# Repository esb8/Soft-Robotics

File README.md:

# Soft Robotics PCB

Motor control, optical feedback, ADCs, sensors, servos, and a camera on a single board.  
This project features a soft-robotics controller built around an ESP32 with an onboard camera, driver stages for multiple electromagnets, photoresistor sensing, SPI breakouts, and a UART header for easy flashing.

## Features
- **ESP32** (WROOM or WROVER) with **camera module** (OV2640 or similar)
- **4–8 electromagnet channels** with protected low-side MOSFET drivers (PWM capable)
- **Photoresistor (LDR) inputs** with RC dividers → ADC
- **SPI header** (3.3V) for add-ons (external ADCs, sensors, or LED drivers)
- **Dedicated UART header** for flashing (RTS/DTR optional) + **USB-C** or JST-PH power
- **Reverse-polarity & transient protection**, per-channel flyback/snubbers
- **Buck Regulation for 2S LiPos**
- **Mounting + cable-reliefs** sized for soft-robotics rigs
- **Full Codebase** containing all peripheral test code

## Media
### Schematic 

### PCB Layout

### Front View

### Back View

### Setup Guidelines
1. Open ArduinoIDE
2. Set Baud Rate: 115200
3. Set COM to whatever appears on device manager
4. Set board to ESP32S3-Dev Board.
5. The serial monitor must read at 115200 Baud.
### Boot Guide
1. Enter Bootloader
2. Ensure IO46 is pulled down.
3. Pull boot low (Switch ON), Pull Enable Up and Down to reset the ESP32 (Switch On -> Switch Off). During this time firmware can be uploaded.
4. Boot from uploaded code
4. Pull boot high (Switch OFF), Pull Enable Up and Down to reset the ESP32 (Switch On -> Switch Off).

## Pinout
- CAMERA: PINS 4 to 14, 21.
- CAM_SDA: IO20
- CAM_SCL: IO3
- S_PWM: IO1, ADC1_CH0
- SDA: IO42
- SCL: IO41
- XSHUT: IO40
- nFault_A: I039
- nFault_B: IO4
- I_SENSE_A: IO14, ADC_CH3
- I_SENSE_B: IO2, ADC1_CH0
- IN1_A: IO38
- IN2_A: IO48
- IN1_B: IO47
- IN2_B: IO21
- LDR1: IO19
- LDR2: IO5
  
## Calculations

### Trip Current (typ.)
I_TRIP = V_REF / (R_IPROPI × A_IPROPI)  
       = 3.3 / (2350 × 455 × 10^-6)  
       ≈ 3.09 A

### IPROPI Current at Trip
I_IPROPI = I_TRIP × A_IPROPI  
         = V_REF / R_IPROPI  
         = 3.3 / 2350  
         ≈ 1.40 mA

### IPROPI Voltage at Trip
V_IPROPI = I_IPROPI × R_IPROPI  
         = 3.3 V

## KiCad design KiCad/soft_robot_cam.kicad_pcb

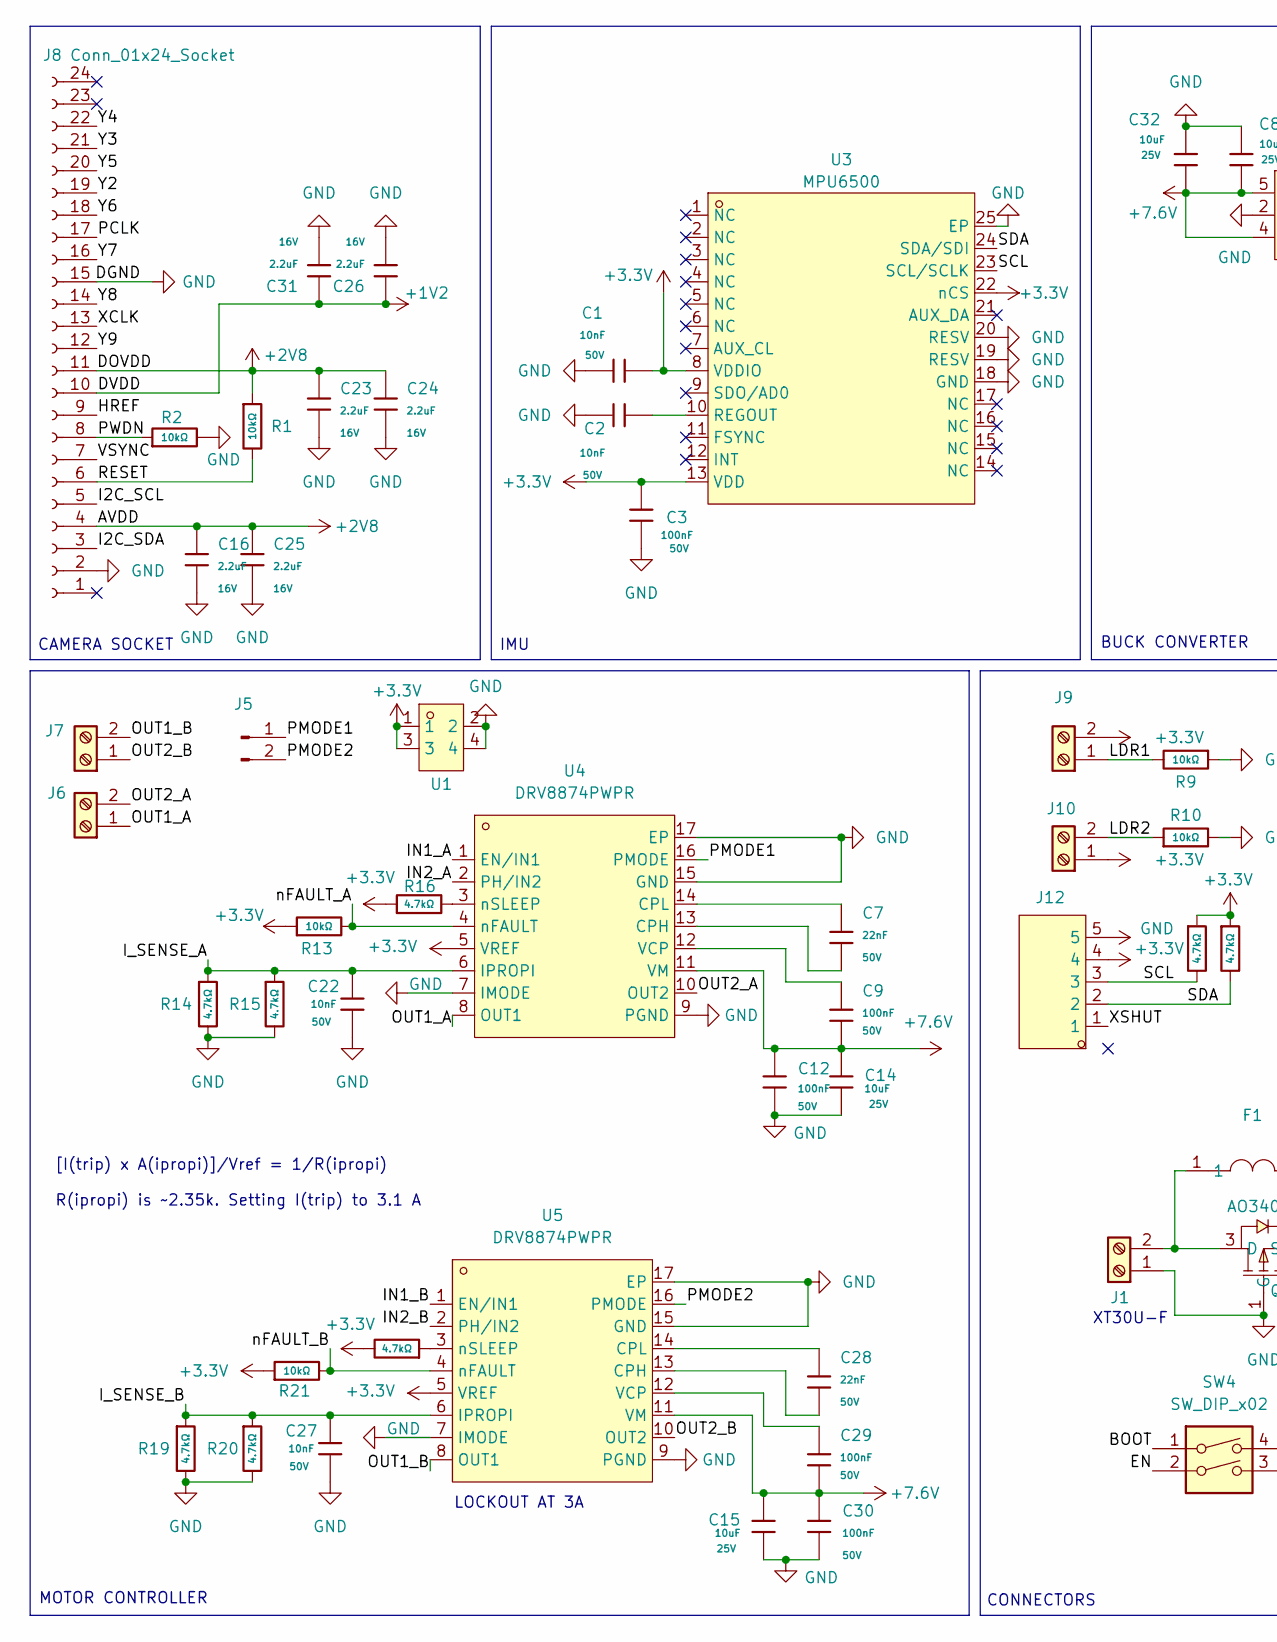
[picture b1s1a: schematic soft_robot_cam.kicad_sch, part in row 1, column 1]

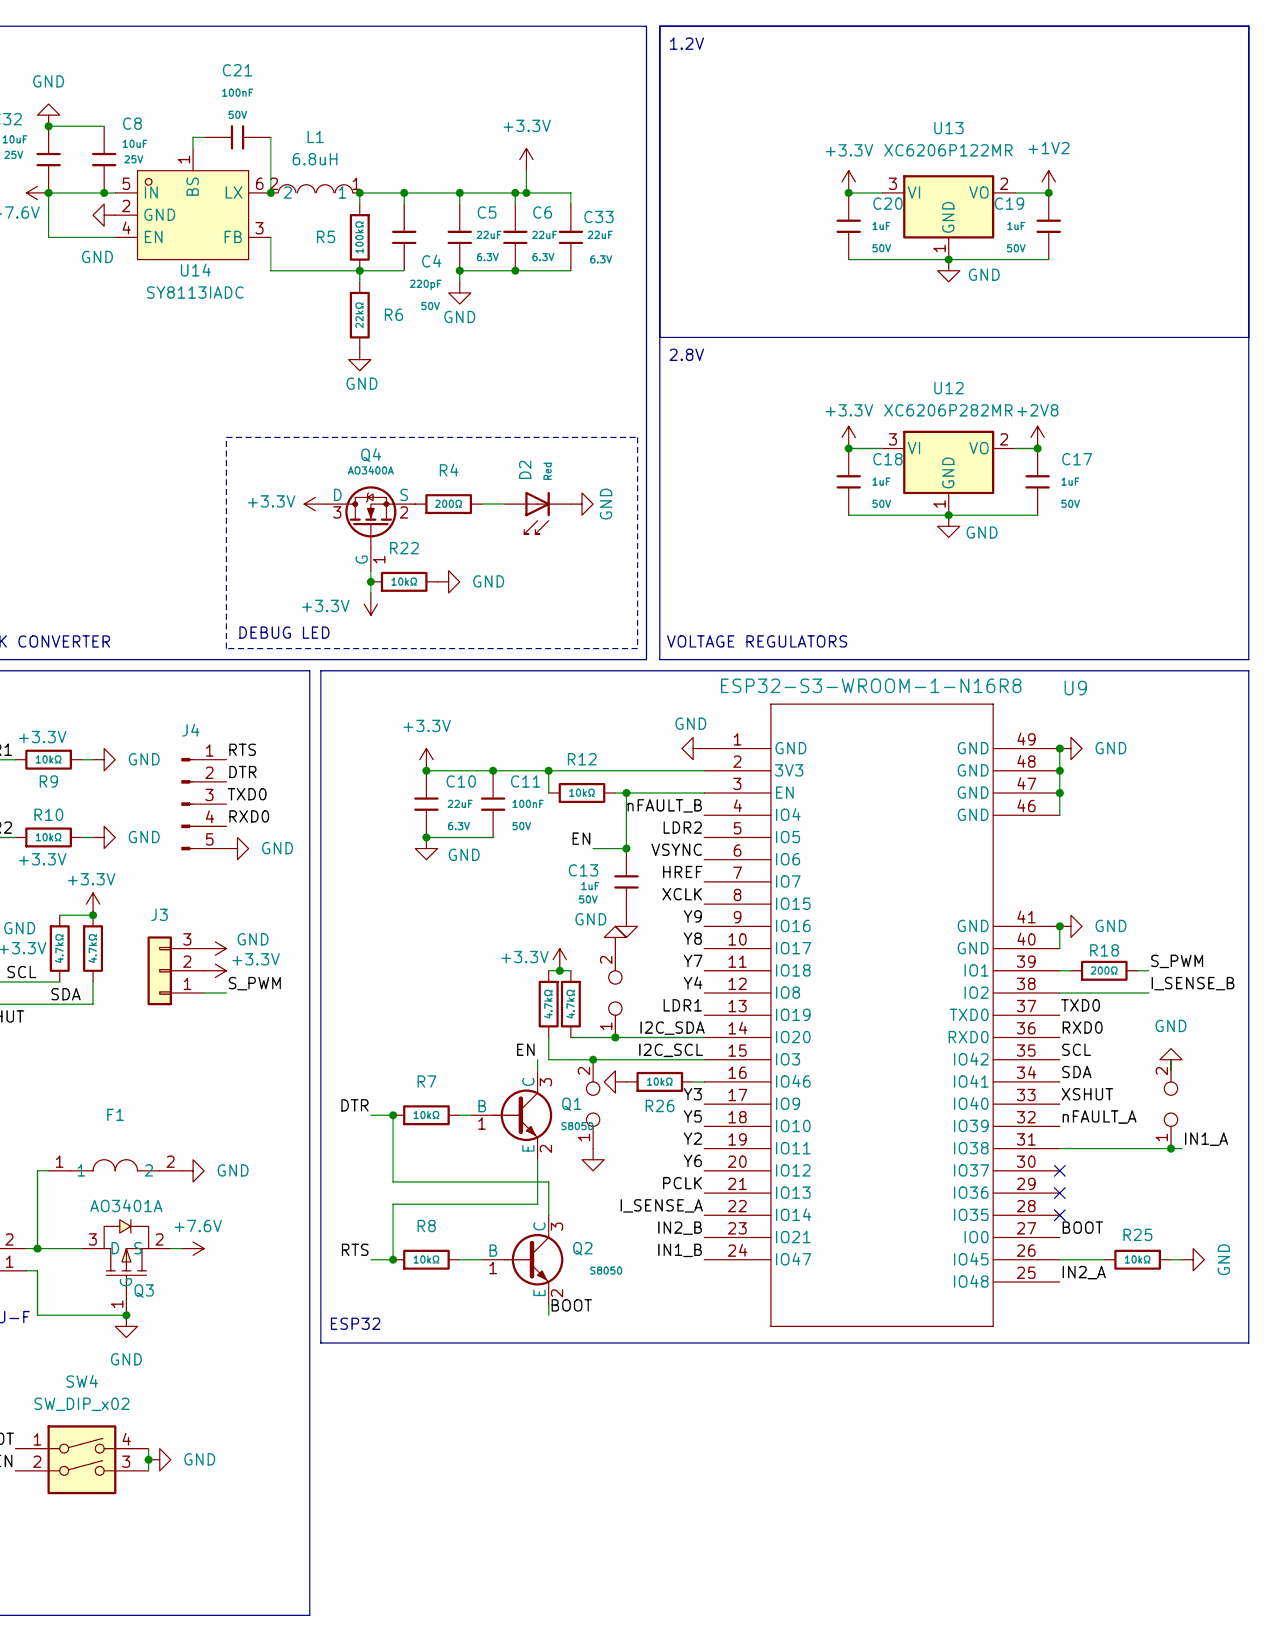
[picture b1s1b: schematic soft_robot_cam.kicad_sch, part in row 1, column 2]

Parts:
C1, C2, C22, C27: 10nF; C_0603; Voltage Rated 50V; Tolerance ±10%; Part 0603B103K500NT; LCSC C57112
C3, C9, C11, C12, C21, C29, C30: 100nF; C_0603; Voltage Rated 50V; Tolerance ±10%; Part CC0603KRX7R9BB104; LCSC C14663
C4: 220pF; C_0402; Voltage Rated 50V; Tolerance ±10%; Part 0402B221K500NT; LCSC C1530
C5, C6, C10, C33: 22uF; C_0603; Voltage Rated 6.3V; Tolerance ±20%; Part CL10A226MQ8NRNC; LCSC C59461
C7, C28: 22nF; C_0603; Voltage Rated 50V; Tolerance ±10%; Part CL10B223KB8NNNC; LCSC C21122
C8, C14, C15, C32: 10uF; C_0603; Voltage Rated 25V; Tolerance ±20%; Part CL10A106MA8NRNC; LCSC C96446
C13, C17, C18, C19, C20: 1uF; C_0603; Voltage Rated 50V; Tolerance ±10%; Part CL10A105KB8NNNC; LCSC C15849
C16, C23, C24, C25, C26, C31: 2.2uF; C_0603; Voltage Rated 16V; Tolerance ±10%; Part CL10A225KO8NNNC; LCSC C23630
D2: Red; D_0603; Part KT-0603R; LCSC C2286
F1: BHFUSE BSMD1206C-1700T; F1206; LCSC Part C41367230
J1: Connector; AMASS_XT30U-F_1x02_P5.0mm_Vertical; LCSC C99102
J3: Conn_01x03; JST_B3B-PH-K-S; LCSC C131339
J4: Conn_01x05_Pin; PinHeader_1x05_P1.27mm_Vertical; LCSC C5243685
J5: Conn_01x02_Pin; HDR-TH_2P-P1.27-V-M; LCSC C5243682
J6, J7, J9, J10: Screw_Terminal_01x02; JST_B2B-PH-K-S; LCSC C131337
J8: Conn_01x24_Socket; FPC-SMD_AFC07-S24ECA-00; LCSC C262643
J12: B5B-PH-K-S-(LF)(SN); CONN-TH_B5B-PH-K-S-LF-SN; LCSC Part C157993
L1: 6.8uH; IND-SMD_L6.0-W6.0; LCSC C341066
Q1, Q2: S8050; Q_SOT-23; Part S8050; LCSC C364312
Q3: AO3401A; SOT-23_L2.9-W1.3-P1.90-LS2.4-BR; LCSC Part C15127
Q4: AO3400A; Q_SOT-23; Part AO3400A; LCSC C20917
R1, R2, R7, R8, R9, R10, R12, R13, R21, R22, R25, R26: 10kΩ; R_0603; Overload Voltage (Max) 75V; Tolerance ±1%; Part 0603WAF1002T5E; LCSC C25804
R3, R11, R14, R15, R16, R17, R19, R20, R23, R24: 4.7kΩ; R_0603; Overload Voltage (Max) 75V; Tolerance ±1%; Part 0603WAF4701T5E; LCSC C23162
R4, R18: 200Ω; R_0402; Overload Voltage (Max) 50V; Tolerance ±1%; Part 0402WGF2000TCE; LCSC C25087
R5: 100kΩ; R_0402; Overload Voltage (Max) 50V; Tolerance ±1%; Part 0402WGF1003TCE; LCSC C25741
R6: 22kΩ; R_0402; Overload Voltage (Max) 50V; Tolerance ±1%; Part 0402WGF2202TCE; LCSC C25768
SW4: SW_DIP_x02; SW-SMD_4P_DSHP02TSGET; LCSC C40735
TP2, TP3, TP4: TestPoint_2Pole
U1: PZ127-2-02-Z; HDR-TH_4P-P1.27-V-M-R2-C2-S1.27_MH127V-12-04-0820; LCSC Part C5372806
U3: MPU6500; QFN-24-1EP_3x3mm_P0.4mm_EP1.75x1.6mm; LCSC C50278
U4, U5: DRV8874PWPR; HTSSOP-16_L5.0-W4.4-P0.65-LS6.4-BL-EP; LCSC Part C1855818
U9: ESP32-S3-WROOM-1-N16R8; ESP32-S3-WROOM-1_EXP; LCSC C2913202
U12: XC6206P282MR; SOT-23-3; LCSC C14255
U13: XC6206P122MR; SOT-23-3; LCSC C2827649
U14: SY8113IADC; TSOT-23-6_L2.9-W1.6-P0.95-LS2.8-BL; LCSC C479075

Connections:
+1V2: C19.1, C26.1, C31.1, J8.10, U13.2 (VO)
+2V8: C16.1, C17.1, C23.1, C24.1, C25.1, J8.4, J8.11, R1.1, U12.2 (VO)
+3.3V: C1.2, C3.2, C4.1, C5.1, C6.1, C10.1, C11.1, C18.1, C20.1, C33.1, J3.2, J9.2, J10.1, J12.4, L1.1, Q4.1 (G), Q4.3 (D), R3.1, R5.1, R11.1, R12.1, R13.1, R16.1, R17.2, R21.1, R22.1, R23.1, R24.1, U1.1, U1.3, U3.8 (VDDIO), U3.13 (VDD), U3.22 (nCS), U4.5 (VREF), U5.5 (VREF), U9.2 (3V3), U12.3 (VI), U13.3 (VI)
+7.6V: C8.2, C9.2, C12.1, C14.1, C15.1, C29.2, C30.1, C32.2, Q3.2 (S), U4.11 (VM), U5.11 (VM), U14.4 (EN), U14.5 (IN); also elsewhere on the board
/BOOT: Q2.2 (E), SW4.1, U9.27 (IO0)
/DTR: J4.2, Q2.3 (C), R7.1
/EN: C13.1, Q1.3 (C), R12.2, SW4.2, U9.3 (EN)
/HREF: J8.9, U9.7 (IO7)
/I2C_SCL: J8.5, R3.2, TP3.2, U9.15 (IO3)
/I2C_SDA: J8.3, R24.2, TP4.1, U9.14 (IO20)
/IN1_A: TP2.1, U4.1 (EN/IN1), U9.31 (IO38); also elsewhere on the board
/IN1_B: U5.1 (EN/IN1), U9.24 (IO47); also elsewhere on the board
/IN2_A: U4.2 (PH/IN2), U9.25 (IO48)
/IN2_B: U5.2 (PH/IN2), U9.23 (IO21)
/I_SENSE_A: C22.2, R14.1, R15.1, U4.6 (IPROPI), U9.22 (IO14)
/I_SENSE_B: C27.2, R19.1, R20.1, U5.6 (IPROPI), U9.38 (IO2)
/LDR1: J9.1, R9.2, U9.13 (IO19)
/LDR2: J10.2, R10.1, U9.5 (IO5)
/OUT1_A: J6.1, U4.8 (OUT1)
/OUT1_B: J7.2, U5.8 (OUT1)
/OUT2_A: J6.2, U4.10 (OUT2)
/OUT2_B: J7.1, U5.10 (OUT2)
/PCLK: J8.17, U9.21 (IO13)
/PMODE1: J5.1, U4.16 (PMODE)
/PMODE2: J5.2, U5.16 (PMODE)
/PWDN: J8.8, R2.1
/RESET: J8.6, R1.2
/RTS: J4.1, Q1.2 (E), R8.1
/RXD0: J4.4, U9.36 (RXD0)
/SCL: J12.3, R11.2, U3.23 (SCL/SCLK), U9.35 (IO42)
/SDA: J12.2, R23.2, U3.24 (SDA/SDI), U9.34 (IO41)
/S_PWM: J3.1, R18.2
/TXD0: J4.3, U9.37 (TXD0)
/VSYNC: J8.7, U9.6 (IO6)
/XCLK: J8.13, U9.8 (IO15)
/XSHUT: J12.1, U9.33 (IO40)
/Y2: J8.19, U9.19 (IO11)
/Y3: J8.21, U9.17 (IO9)
/Y4: J8.22, U9.12 (IO8)
/Y5: J8.20, U9.18 (IO10)
/Y6: J8.18, U9.20 (IO12)
/Y7: J8.16, U9.11 (IO18)
/Y8: J8.14, U9.10 (IO17)
/Y9: J8.12, U9.9 (IO16)
/nFAULT_A: R13.2, U4.4 (nFAULT), U9.32 (IO39)
/nFAULT_B: R21.2, U5.4 (nFAULT), U9.4 (IO4)
unnamed: D2.2, R4.2
unnamed: Q1.1 (B), R7.2
unnamed: Q2.1 (B), R8.2
unnamed: Q4.2 (S), R4.1
unnamed: C2.2, U3.10 (REGOUT)
unnamed: C7.2, U4.13 (CPH)
unnamed: C7.1, U4.14 (CPL)
unnamed: C9.1, U4.12 (VCP)
unnamed: R16.2, U4.3 (nSLEEP)
unnamed: C28.2, U5.13 (CPH)
unnamed: C28.1, U5.14 (CPL)
unnamed: C29.1, U5.12 (VCP)
unnamed: R17.1, U5.3 (nSLEEP)
unnamed: R18.1, U9.39 (IO1)
unnamed: R25.2, U9.26 (IO45)
unnamed: R26.2, U9.16 (IO46)
unnamed: C21.1, U14.1 (BS)
unnamed: C4.2, R5.2, R6.1, U14.3 (FB)
unnamed: C21.2, L1.2, U14.6 (LX)

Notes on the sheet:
IMU
ESP32
XT30U-F
DEBUG LED
1.2V
MOTOR CONTROLLER
2.8V
CAMERA SOCKET
BUCK CONVERTER
CONNECTORS
VOLTAGE REGULATORS
[I(trip) x A(ipropi)]/Vref = 1/R(ipropi) R(ipropi) is ~2.35k. Setting I(trip) to 3.1 A
LOCKOUT AT 3A

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
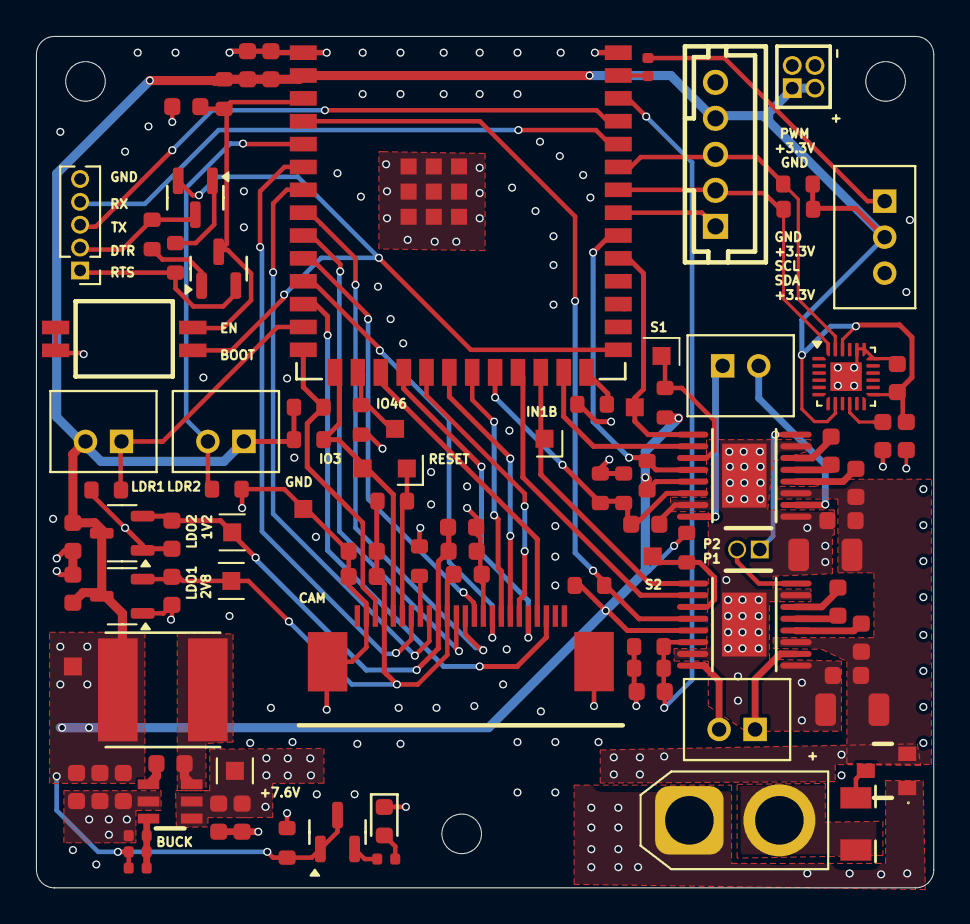
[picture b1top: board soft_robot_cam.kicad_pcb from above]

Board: 4 copper layers, 49.8 x 47.3 mm, 89 parts (0 on the bottom side), 68 nets.

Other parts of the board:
+7.6V, +7.6V#2, +7.6V#3: TestPoint_Pad_1.0x1.0mm
C34, C35: 10uF; C_1206
GND: TestPoint_Pad_1.0x1.0mm
GND#2: TestPoint_Pad_1.0x1.0mm

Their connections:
+7.6V: +7.6V.1, C34.1, C35.1; also elsewhere on the board
/IN1_A: GND#2.1; also elsewhere on the board
/IN1_B: GND.1; also elsewhere on the board

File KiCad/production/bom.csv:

Designator,Footprint,Quantity,Value,LCSC Part #
"C1, C2, C22, C27",C_0603,4,10nF,C57112
"C10, C33, C5, C6",C_0603,4,22uF,C59461
"C11, C12, C21, C29, C3, C30, C9",C_0603,7,100nF,C14663
"C13, C17, C18, C19, C20",C_0603,5,1uF,C15849
"C23, C24, C25, C26, C31",C_0603,5,2.2uF,C23630
"C28, C7",C_0603,2,22nF,C21122
"C32, C8",C_0603,2,10uF,C96446
"C34, C35",C_1206,2,10uF,C13585
C4,C_0402,1,220pF,C1530
D2,D_0603,1,Red,C2286
F1,F1206,1,BHFUSE BSMD1206C-1700T,C41367230
J1,AMASS_XT30U-F_1x02_P5.0mm_Vertical,1,Connector,C99102
"J10, J6, J7, J9",JST_B2B-PH-K-S,4,Screw_Terminal_01x02,C131337
J12,CONN-TH_B5B-PH-K-S-LF-SN,1,B5B-PH-K-S-(LF)(SN),C157993
J3,JST_B3B-PH-K-S,1,Conn_01x03,C131339
J4,PinHeader_1x05_P1.27mm_Vertical,1,Conn_01x05_Pin,C5243685
J5,HDR-TH_2P-P1.27-V-M,1,Conn_01x02_Pin,C5243682
J8,FPC-SMD_AFC07-S24ECA-00,1,Conn_01x24_Socket,C262643
L1,IND-SMD_L6.0-W6.0,1,6.8uH,C341066
"Q1, Q2",Q_SOT-23,2,S8050,C364312
Q3,SOT-23_L2.9-W1.3-P1.90-LS2.4-BR,1,AO3401A,C15127
Q4,Q_SOT-23,1,AO3400A,C20917
"R1, R10, R12, R13, R2, R21, R22, R25, R26, R7, R8, R9",R_0603,12,10kΩ,C25804
"R11, R14, R15, R16, R17, R19, R20, R23, R24, R3",R_0603,10,4.7kΩ,C23162
"R18, R4",R_0402,2,200Ω,C25087
R5,R_0402,1,100kΩ,C25741
R6,R_0402,1,22kΩ,C25768
SW4,SW-SMD_4P_DSHP02TSGET,1,SW_DIP_x02,C40735
U1,HDR-TH_4P-P1.27-V-M-R2-C2-S1.27_MH127V-12-04-0820,1,PZ127-2-02-Z,C5372806
U12,SOT-23-3,1,XC6206P282MR,C14255
U13,SOT-23-3,1,XC6206P122MR,
U14,TSOT-23-6_L2.9-W1.6-P0.95-LS2.8-BL,1,SY8113IADC,C479075 
U3,QFN-24-1EP_3x3mm_P0.4mm_EP1.75x1.6mm,1,MPU6500,C50278
"U4, U5",HTSSOP-16_L5.0-W4.4-P0.65-LS6.4-BL-EP,2,DRV8874PWPR,C1855818
U9,ESP32-S3-WROOM-1_EXP,1,ESP32-S3-WROOM-1-N16R8,C2913202

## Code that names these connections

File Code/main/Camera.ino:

#include "esp_camera.h"
#define CAMERA_MODEL_ESP32S3_EYE
#include "camera.h"

void cameraSetup() {
  Serial.begin(115200);
  delay(1000);

  Serial.println("Starting ESP32-S3 camera...");

  camera_config_t config;
  config.ledc_channel = LEDC_CHANNEL_0;
  config.ledc_timer   = LEDC_TIMER_0;
  config.pin_d0       = Y2_GPIO_NUM;
  config.pin_d1       = Y3_GPIO_NUM;
  config.pin_d2       = Y4_GPIO_NUM;
  config.pin_d3       = Y5_GPIO_NUM;
  config.pin_d4       = Y6_GPIO_NUM;
  config.pin_d5       = Y7_GPIO_NUM;
  config.pin_d6       = Y8_GPIO_NUM;
  config.pin_d7       = Y9_GPIO_NUM;
  config.pin_xclk     = XCLK_GPIO_NUM;
  config.pin_pclk     = PCLK_GPIO_NUM;
  config.pin_vsync    = VSYNC_GPIO_NUM;
  config.pin_href     = HREF_GPIO_NUM;
  config.pin_sccb_sda = SIOD_GPIO_NUM;
  config.pin_sccb_scl = SIOC_GPIO_NUM;
  config.pin_pwdn     = PWDN_GPIO_NUM;
  config.pin_reset    = RESET_GPIO_NUM;
  config.xclk_freq_hz = 20000000;
  config.frame_size   = FRAMESIZE_QVGA;   // 320x240 (safe for testing)
  config.pixel_format = PIXFORMAT_JPEG;  // JPEG output
  config.grab_mode    = CAMERA_GRAB_WHEN_EMPTY;
  config.fb_location  = CAMERA_FB_IN_PSRAM;
  config.jpeg_quality = 12;
  config.fb_count     = 1;

  if (psramFound()) {
    config.jpeg_quality = 10;
    config.fb_count     = 2;
    config.grab_mode    = CAMERA_GRAB_LATEST;
  }

  esp_err_t err = esp_camera_init(&config);
  if (err != ESP_OK) {
    Serial.printf("Camera init failed! Error 0x%x\n", err);
    while (true) { delay(1000); }
  }

  Serial.println("Camera init successful!");
}

void cameraCapture() {
  // Capture one frame
  camera_fb_t *fb = esp_camera_fb_get();
  if (!fb) {
    Serial.println("Frame capture failed");
    delay(2000);
    return;
  }

  Serial.printf("Captured image: %d bytes (%dx%d)\n", fb->len, fb->width, fb->height);

  // Always return frame buffer when done
  esp_camera_fb_return(fb);

  delay(3000); // wait before capturing next frame
}

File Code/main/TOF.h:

#pragma once
#include <Arduino.h>
#include <Wire.h>
#include "Adafruit_VL53L0X.h"

// --- Pin mapping ---
#define PIN_I2C_SDA 41
#define PIN_I2C_SCL 42
#define PIN_XSHUT   40

// --- Global sensor object ---
extern Adafruit_VL53L0X lox;

// --- Functions ---
bool vl53Init();
int  vl53ReadDistance();   // returns distance in mm, or -1 if fail

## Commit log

2025-08-13 Major overhaul to layout, changed ESP to support more GPIOs, changed IMU to be standardized, changed LDOs to support the correct amperage, added buck converter for shifting LiPo voltage to 3.3V.
2025-08-14 Completed the schematic, began layout
2025-08-15 Restitched old board, last version with old board attached, finalized layout aside from PMODE connectors.
2025-08-15 Added most 3D models, revised some layout based off 3D model placement, need to verify JST-XH placement and ensure no design errors.
2025-08-15 Reviewed connector placement, chaning footprint to ensure clearance, added LEDs on Buck, slightly modified layout to improve spacing and clearance. Next is a full design and BOM review.
2025-08-23 Reviewed and fixed wiring, adding eFuses and protection IC.
2025-08-25 fixes to schematic regarding ESP32 pins, cleaned up layout
2025-08-25 Minor additions to PCB Layout, added branding and text
2025-08-25 Minor Changes
2025-08-25 Removed locked schematic
2025-08-26 Cleaned Up BOM
2025-08-26 Critical Fixes
2025-08-26 Fixes the layout
2025-08-26 Production ready PCB
2025-09-06 Fixed Fuse, Added more testpads, changed xt30 to male, added switch in schematic for GPIO3
2025-09-16 Feat: Added validation code for drv, imu, servo, cam
    Fix: Organized Git Repo
2025-09-17 Feat: Added TOF code
2025-09-24 Fix: Camera.h
2025-09-24 chore: Remove old code
2025-09-24 feat: Convert to platformio
2025-10-01 feat: added documentation, schematic photos and PCB layout to README for easier debugging.
